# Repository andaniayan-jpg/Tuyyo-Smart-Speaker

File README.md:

# Tuyyo-Smart-Speaker

**TUYO is a compact, AI-powered voice assistant speaker that was designed and built completely from scratch. It combines custom embedded hardware with modern AI to create a portable assistant that can listen, process speech, and respond in real time.**

# How to use it
-Power the device using a LiPo battery or USB-C connection.

-Ensure the system handling AI processing is connected.

-Speak clearly into the microphone.

-The device captures and processes your voice.

-The AI generates a response.

-The response is played through the speaker.

The interaction is designed to feel natural, similar to existing voice assistants.
# Components used
1. ESP32-WROOM-32 (Main Cintroller)
   -This is the brain of Tuyyo
   - Processes the input from the microphone
   - Sends data to the AI system
   - Receives responsee
   - Controls audio output with amplifier.
   - Handles system Logic and connects all other components.

  2. ICS-43434 I2S Microphone
  - This is a digital microphone used to capture voice output.
  - Convertes sound to digital signals.
  - Sends audio data to ESP32 using I2S protocol
  - Provides clear and noise-resistant audio input.

 3. MAX98357A I2S Audio Amplifier.
    - Recives data from ESP32.
    - Coverts to analog signal.
    - Enables clear audio output.
4. Speaker
   - Converts electrical signals into sound
   - Plays AI-generated responses
  
5. TP4056
   - Charges the battery from Usb-c port.

6. LiPO battery
   - Provides portable power
   - Replaceble
7. AMS1117-3.3 Voltage regulator
   - Converts 5V to 3.3V
   - Supplies power to ESP32 and other components that require 3.3V.
8. CH340C USB to UART.
   - Converts USB signal.
   - Helps in programming the ESP32.
9. USB-C RECEPTABLE
   - Provides 5v power to the system.
   - Allows connection to computer and charger.
10. APA-106-F5
11. FerriteBead
12. Resistors and Capacitors.

   # This project was created to explore the connection between hardware engineering and artificial intelligence.
   Rather than relying on existing smart speaker platforms, the goal was to understand and rebuild the entire system from the ground up. That meant designing the PCB, choosing the right components, managing power delivery, and integrating AI-based voice interaction into a working physical product.

   # What makes TUYO unique
-Fully custom-designed PCB

-Integration of AI with embedded systems

-Compact and portable design

-Clear separation of input, processing, and output

-Built from scratch as a complete system

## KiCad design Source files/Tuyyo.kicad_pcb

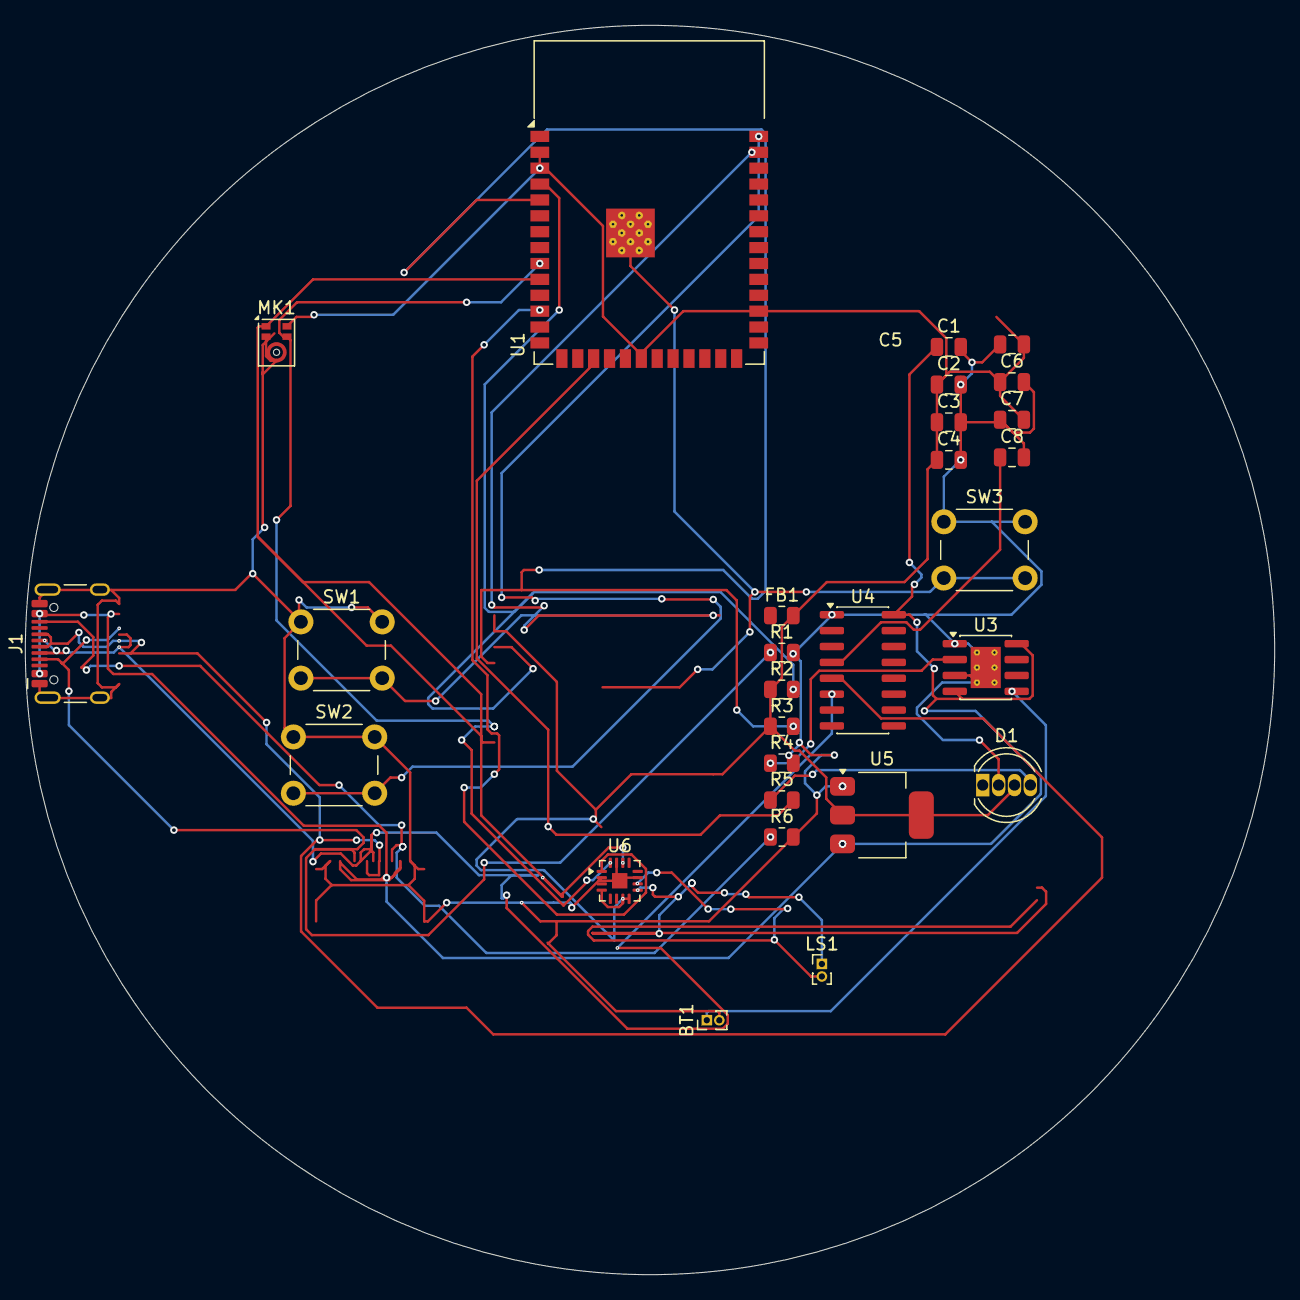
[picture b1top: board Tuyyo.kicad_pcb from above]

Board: 2 copper layers, 99.9 x 99.9 mm, 28 parts (0 on the bottom side), 22 nets.

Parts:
BT1: Battery; PinHeader_1x02_P1.00mm_Vertical
C1, C2, C3, C4, C5, C6, C7, C8: 0.1 µF; C_0805_2012Metric
D1: APA-106-F5; LED_D5.0mm-4_RGB
FB1: FerriteBead; R_0805_2012Metric
J1: USB_C_Receptacle_USB2.0_14P; USB_C_Receptacle_HCTL_HC-TYPE-C-16P-01A
LS1: Speaker; PinHeader_1x02_P1.00mm_Vertical
MK1: ICS-43434; Knowles_LGA-5_3.5x2.65mm
R1, R6: 5.1kΩ; R_0805_2012Metric
R2, R3: 10kΩ; R_0805_2012Metric
R4: 1.2kΩ; R_0805_2012Metric
R5: 330kΩ; R_0805_2012Metric
SW1, SW2, SW3: SW_Push; SW_PUSH_6mm_H4.3mm
U1: ESP32-S3; ESP32-S3-WROOM-1
U3: TP4056-42-ESOP8; SOIC-8-1EP_3.9x4.9mm_P1.27mm_EP2.41x3.3mm_ThermalVias
U4: CH340C; SOIC-16_3.9x9.9mm_P1.27mm
U5: AMS1117-3.3; SOT-223-3_TabPin2
U6: MAX98357A; TQFN-16-1EP_3x3mm_P0.5mm_EP1.23x1.23mm

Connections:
+3.3V: C2.1, C3.1, C4.1, C5.2, C6.1, C7.2, D1.3 (VDD), FB1.2, MK1.5 (VDD), R2.1, R3.1, U1.2 (VDD3P3), U1.3 (VDD3P3), U1.20 (VDD3P3_RTC), U1.29 (VDD_SPI), U5.2 (VO), U6.4 (~SD_MODE), U6.7 (VDD), U6.8 (VDD)
/5V RAIL: C1.1, J1.A4 (VBUS), J1.A9 (VBUS), J1.B4 (VBUS), J1.B9 (VBUS), U3.4 (V_{CC}), U3.8 (CE), U4.16 (VCC), U5.3 (VI)
/B+: BT1.1 (+), U3.5 (BAT)
/CC1: J1.A5 (CC1), R1.1
/CC2: J1.B5 (CC2), R6.1
/D+: J1.A6 (D+), J1.B6 (D+), U4.5 (UD+)
/D-: J1.A7 (D-), J1.B7 (D-), U4.6 (UD-)
/EN: R2.2, U1.4 (CHIP_PU)
/GPIO4: MK1.4 (SCK), U1.9 (GPIO4), U6.16 (BCLK)
/GPIO5: MK1.1 (WS), U1.10 (GPIO5), U6.14 (LRCLK)
/GPIO7: U1.12 (GPIO7), U6.1 (DIN)
/GPIO12: R5.2, U1.17 (GPIO12)
/GPIO34: SW1.2, U1.39 (GPIO34)
/GPIO35: SW2.2, U1.40 (GPIO35)
/GPIO36: SW3.2, U1.41 (GPIO36)
/IO0: R3.2, U1.5 (GPIO0)
/SPEAKER+: LS1.1, U6.9 (OUTP)
/SPEAKER_: LS1.2, U6.10 (OUTN)
GND: BT1.2 (-), C1.2, C2.2, C3.2, C4.2, C5.1, C6.2, C7.1, C8.2, D1.2 (GND), J1.A1 (GND), J1.A12 (GND), J1.B1 (GND), J1.B12 (GND), J1.S1 (SHIELD), MK1.2 (LR), MK1.3 (GND), R1.2, R4.2, R6.2, SW1.1, SW2.1, SW3.1, U3.1 (TEMP), U3.3 (GND), U3.9 (EPAD), U4.1 (GND), U5.1 (GND), U6.2 (GAIN_SLOT), U6.3 (GND), U6.11 (GND), U6.15 (GND), U6.17 (PAD)
unnamed: D1.4 (DI), R5.1
unnamed: R4.1, U3.2 (PROG)
unnamed: C8.1, U4.4 (V3)

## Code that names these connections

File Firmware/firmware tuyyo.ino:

#include <WiFi.h>
#include "driver/i2s.h"
#include <math.h>

const char* WIFI_SSID = "wifi name";
const char* WIFI_PASSWORD = "wifi password";

const char* AI_SERVER_IP = "192.168.1.10";
const int AI_SERVER_PORT = 5000;

// APA-106 / status LED data pin
#define STATUS_LED_PIN 12

// Push buttons from schematic
#define BUTTON_1 34
#define BUTTON_2 35
#define BUTTON_3 36

// Shared I2S clock pins from schematic
#define I2S_BCLK 4
#define I2S_LRCLK 5

// ICS-43434 microphone data pin
#define MIC_DATA_IN 6

// MAX98357A amplifier data pin
#define SPEAKER_DATA_OUT 7

#define SAMPLE_RATE 16000
#define BUFFER_SIZE 512

#define I2S_PORT I2S_NUM_0

void blinkStatusPin(int times, int delayMs) {
  for (int i = 0; i < times; i++) {
    digitalWrite(STATUS_LED_PIN, HIGH);
    delay(delayMs);
    digitalWrite(STATUS_LED_PIN, LOW);
    delay(delayMs);
  }
}

void connectWiFi() {
  Serial.println();
  Serial.println("Connecting to Wi-Fi...");

  WiFi.mode(WIFI_STA);
  WiFi.begin(WIFI_SSID, WIFI_PASSWORD);

  int attempt = 0;

  while (WiFi.status() != WL_CONNECTED && attempt < 30) {
    delay(500);
    Serial.print(".");
    attempt++;
  }

  Serial.println();

  if (WiFi.status() == WL_CONNECTED) {
    Serial.println("Wi-Fi connected.");
    Serial.print("IP address: ");
    Serial.println(WiFi.localIP());
    blinkStatusPin(3, 150);
  } else {
    Serial.println("Wi-Fi not connected.");
    Serial.println("Continuing in offline hardware test mode.");
    blinkStatusPin(5, 100);
  }
}

void setupI2SAudio() {
  i2s_config_t i2sConfig = {};
  i2sConfig.mode = (i2s_mode_t)(I2S_MODE_MASTER | I2S_MODE_TX | I2S_MODE_RX);
  i2sConfig.sample_rate = SAMPLE_RATE;
  i2sConfig.bits_per_sample = I2S_BITS_PER_SAMPLE_32BIT;
  i2sConfig.channel_format = I2S_CHANNEL_FMT_ONLY_LEFT;
  i2sConfig.communication_format = I2S_COMM_FORMAT_I2S;
  i2sConfig.intr_alloc_flags = ESP_INTR_FLAG_LEVEL1;
  i2sConfig.dma_buf_count = 4;
  i2sConfig.dma_buf_len = 256;
  i2sConfig.use_apll = false;
  i2sConfig.tx_desc_auto_clear = true;
  i2sConfig.fixed_mclk = 0;

  i2s_pin_config_t i2sPins = {};
  i2sPins.bck_io_num = I2S_BCLK;
  i2sPins.ws_io_num = I2S_LRCLK;
  i2sPins.data_out_num = SPEAKER_DATA_OUT;
  i2sPins.data_in_num = MIC_DATA_IN;

  esp_err_t installResult = i2s_driver_install(I2S_PORT, &i2sConfig, 0, NULL);

  if (installResult != ESP_OK) {
    Serial.print("I2S driver install failed. Error code: ");
    Serial.println(installResult);
    return;
  }

  esp_err_t pinResult = i2s_set_pin(I2S_PORT, &i2sPins);

  if (pinResult != ESP_OK) {
    Serial.print("I2S pin setup failed. Error code: ");
    Serial.println(pinResult);
    return;
  }

  i2s_zero_dma_buffer(I2S_PORT);

  Serial.println("I2S audio initialized.");
  Serial.println("Microphone: ICS-43434");
  Serial.println("Amplifier: MAX98357A");
}

void playTestTone() {
  Serial.println("Playing speaker test tone...");

  int frequency = 440;
  int durationMs = 700;
  int totalSamples = (SAMPLE_RATE * durationMs) / 1000;

  size_t bytesWritten;

  for (int i = 0; i < totalSamples; i++) {
    float t = (float)i / SAMPLE_RATE;
    int32_t sample = (int32_t)(60000000 * sin(2.0 * PI * frequency * t));

    i2s_write(I2S_PORT, &sample, sizeof(sample), &bytesWritten, portMAX_DELAY);
  }

  Serial.println("Speaker test tone finished.");
}

int readMicLevel() {
  int32_t buffer[BUFFER_SIZE];
  size_t bytesRead = 0;

  esp_err_t result = i2s_read(
    I2S_PORT,
    buffer,
    sizeof(buffer),
    &bytesRead,
    100 / portTICK_PERIOD_MS
  );

  if (result != ESP_OK || bytesRead == 0) {
    return 0;
  }

  int samplesRead = bytesRead / sizeof(int32_t);
  long total = 0;

  for (int i = 0; i < samplesRead; i++) {
    int32_t sample = buffer[i] >> 14;
    total += abs(sample);
  }

  return total / samplesRead;
}

void readButtons() {
  int button1State = digitalRead(BUTTON_1);
  int button2State = digitalRead(BUTTON_2);
  int button3State = digitalRead(BUTTON_3);

  if (button1State == LOW) {
    Serial.println("Button 1 pressed");
  }

  if (button2State == LOW) {
    Serial.println("Button 2 pressed");
  }

  if (button3State == LOW) {
    Serial.println("Button 3 pressed");
  }
}

void sendAudioToAIServer() {
  Serial.println("AI server communication is planned for the next firmware version.");
}

void setup() {
  Serial.begin(115200);
  delay(1000);

  pinMode(STATUS_LED_PIN, OUTPUT);
  digitalWrite(STATUS_LED_PIN, LOW);

  pinMode(BUTTON_1, INPUT);
  pinMode(BUTTON_2, INPUT);
  pinMode(BUTTON_3, INPUT);

  Serial.println();
  Serial.println("Starting TUYO Smart Speaker firmware...");
  Serial.println("Firmware version: 0.1");
  Serial.println("Board: Custom ESP32-WROOM-32 TUYO PCB");

  Serial.println();
  Serial.println("Pin map:");
  Serial.println("I2S BCLK  -> GPIO4");
  Serial.println("I2S LRCLK -> GPIO5");
  Serial.println("Mic SD    -> GPIO6");
  Serial.println("Speaker DIN -> GPIO7");
  Serial.println("LED/Data  -> GPIO12");
  Serial.println("Buttons   -> GPIO34, GPIO35, GPIO36");

  blinkStatusPin(2, 200);

  connectWiFi();
  setupI2SAudio();
  playTestTone();

  Serial.println();
  Serial.println("Setup complete.");
  Serial.println("Reading microphone levels...");
}

void loop() {
  int micLevel = readMicLevel();

  Serial.print("Mic level: ");
  Serial.println(micLevel);

  readButtons();

  if (micLevel > 500) {
    digitalWrite(STATUS_LED_PIN, HIGH);
  } else {
    digitalWrite(STATUS_LED_PIN, LOW);
  }

  delay(200);
}

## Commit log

2026-04-22 Create J
2026-05-07 Create cad
2026-05-07 Add link to Tuyyo.f3 file
